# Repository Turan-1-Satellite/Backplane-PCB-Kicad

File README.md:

# Turan-1 Backplane PCB in KiCad
## About
This repository contains the KiCad 9.0 project files for the TURAN-1 Backplane PCB.

## Requirements
- KiCad 9.0 or later

## First Set up
All required custom libraries and 3D models are included as a git submodule. To clone the repository together with custom libraries, you need to recursively clone it:
```
git clone --recurse-submodules https://github.com/Turan-1-Satellite/Backplane-PCB-Kicad.git
```

## Open the Project
Open the BP-PCB-Kicad.kicad_pro file from the project root directory.

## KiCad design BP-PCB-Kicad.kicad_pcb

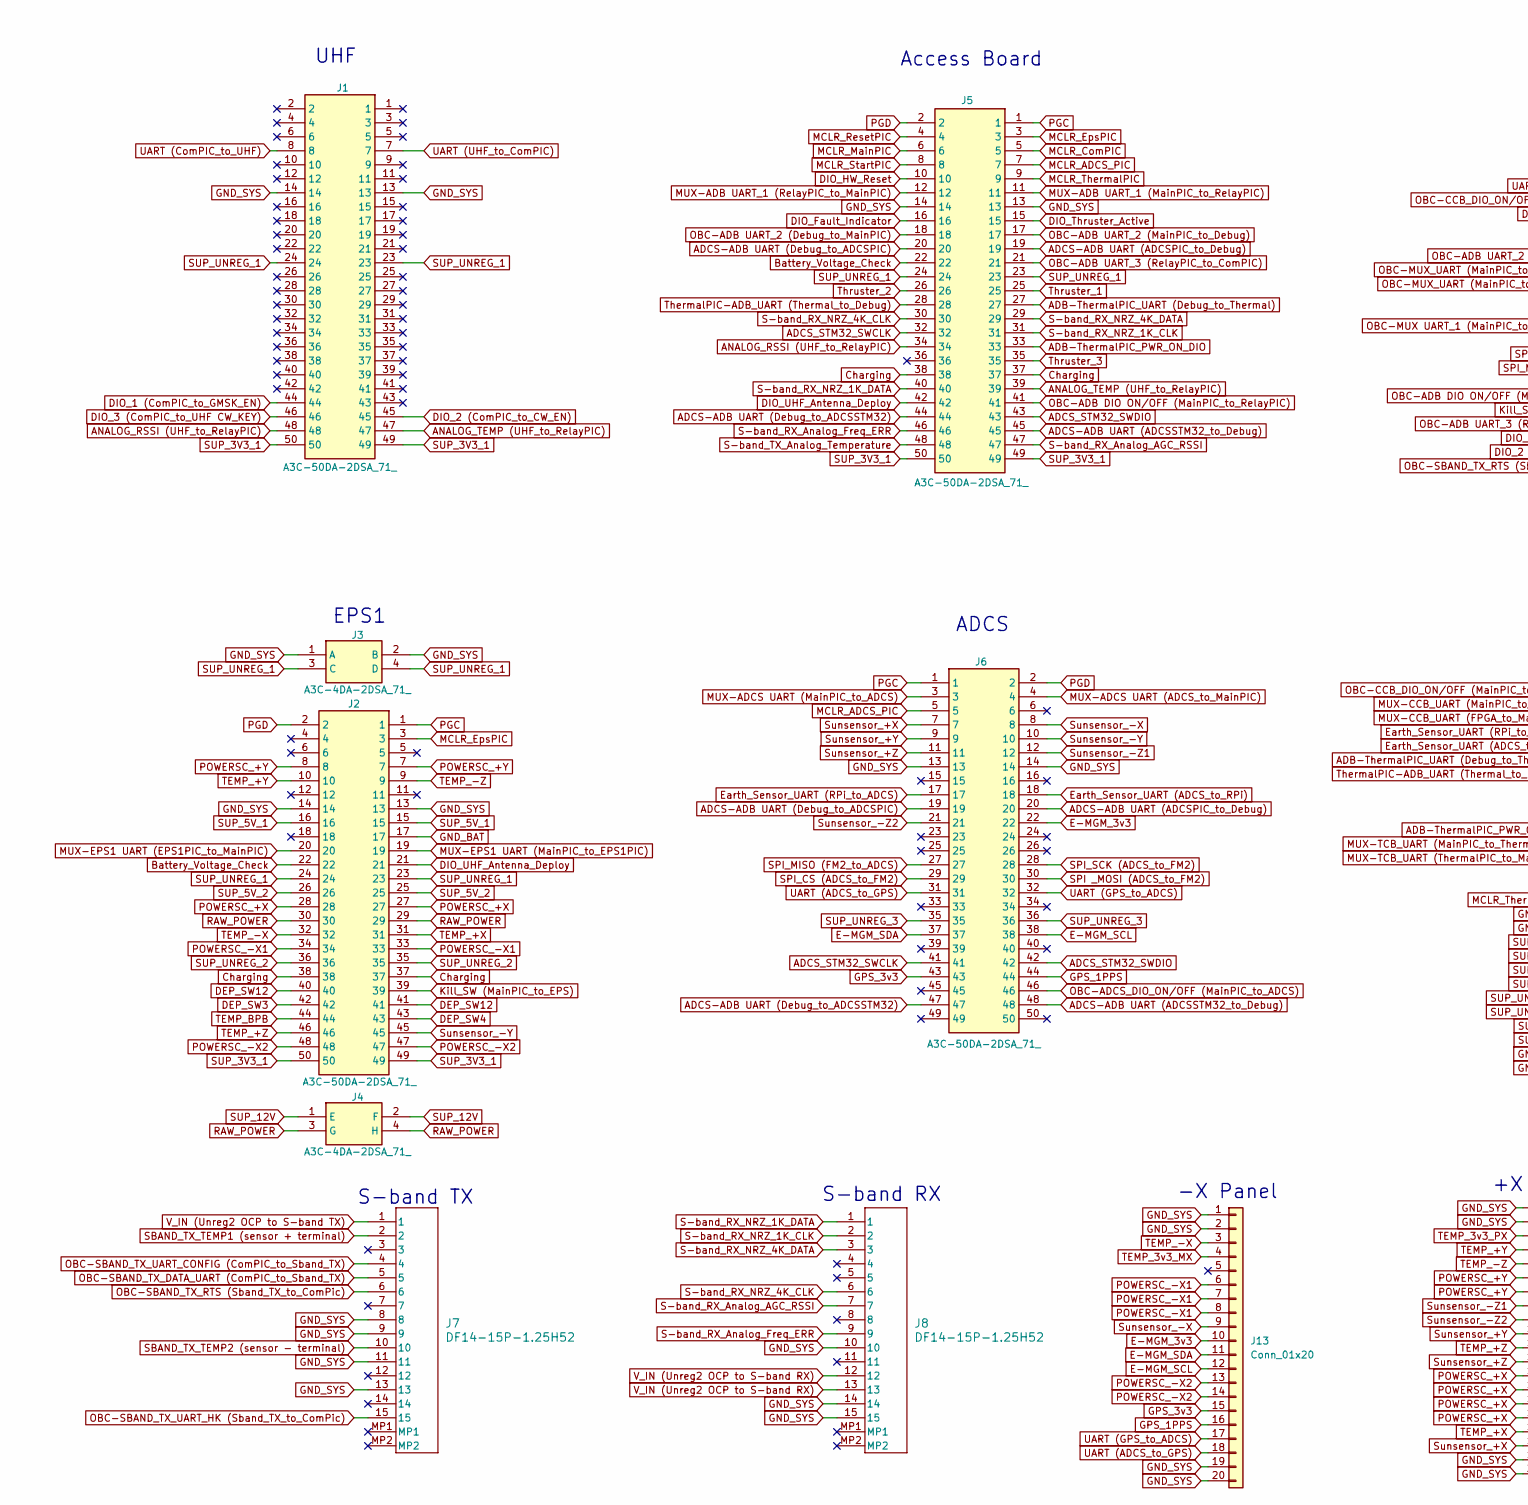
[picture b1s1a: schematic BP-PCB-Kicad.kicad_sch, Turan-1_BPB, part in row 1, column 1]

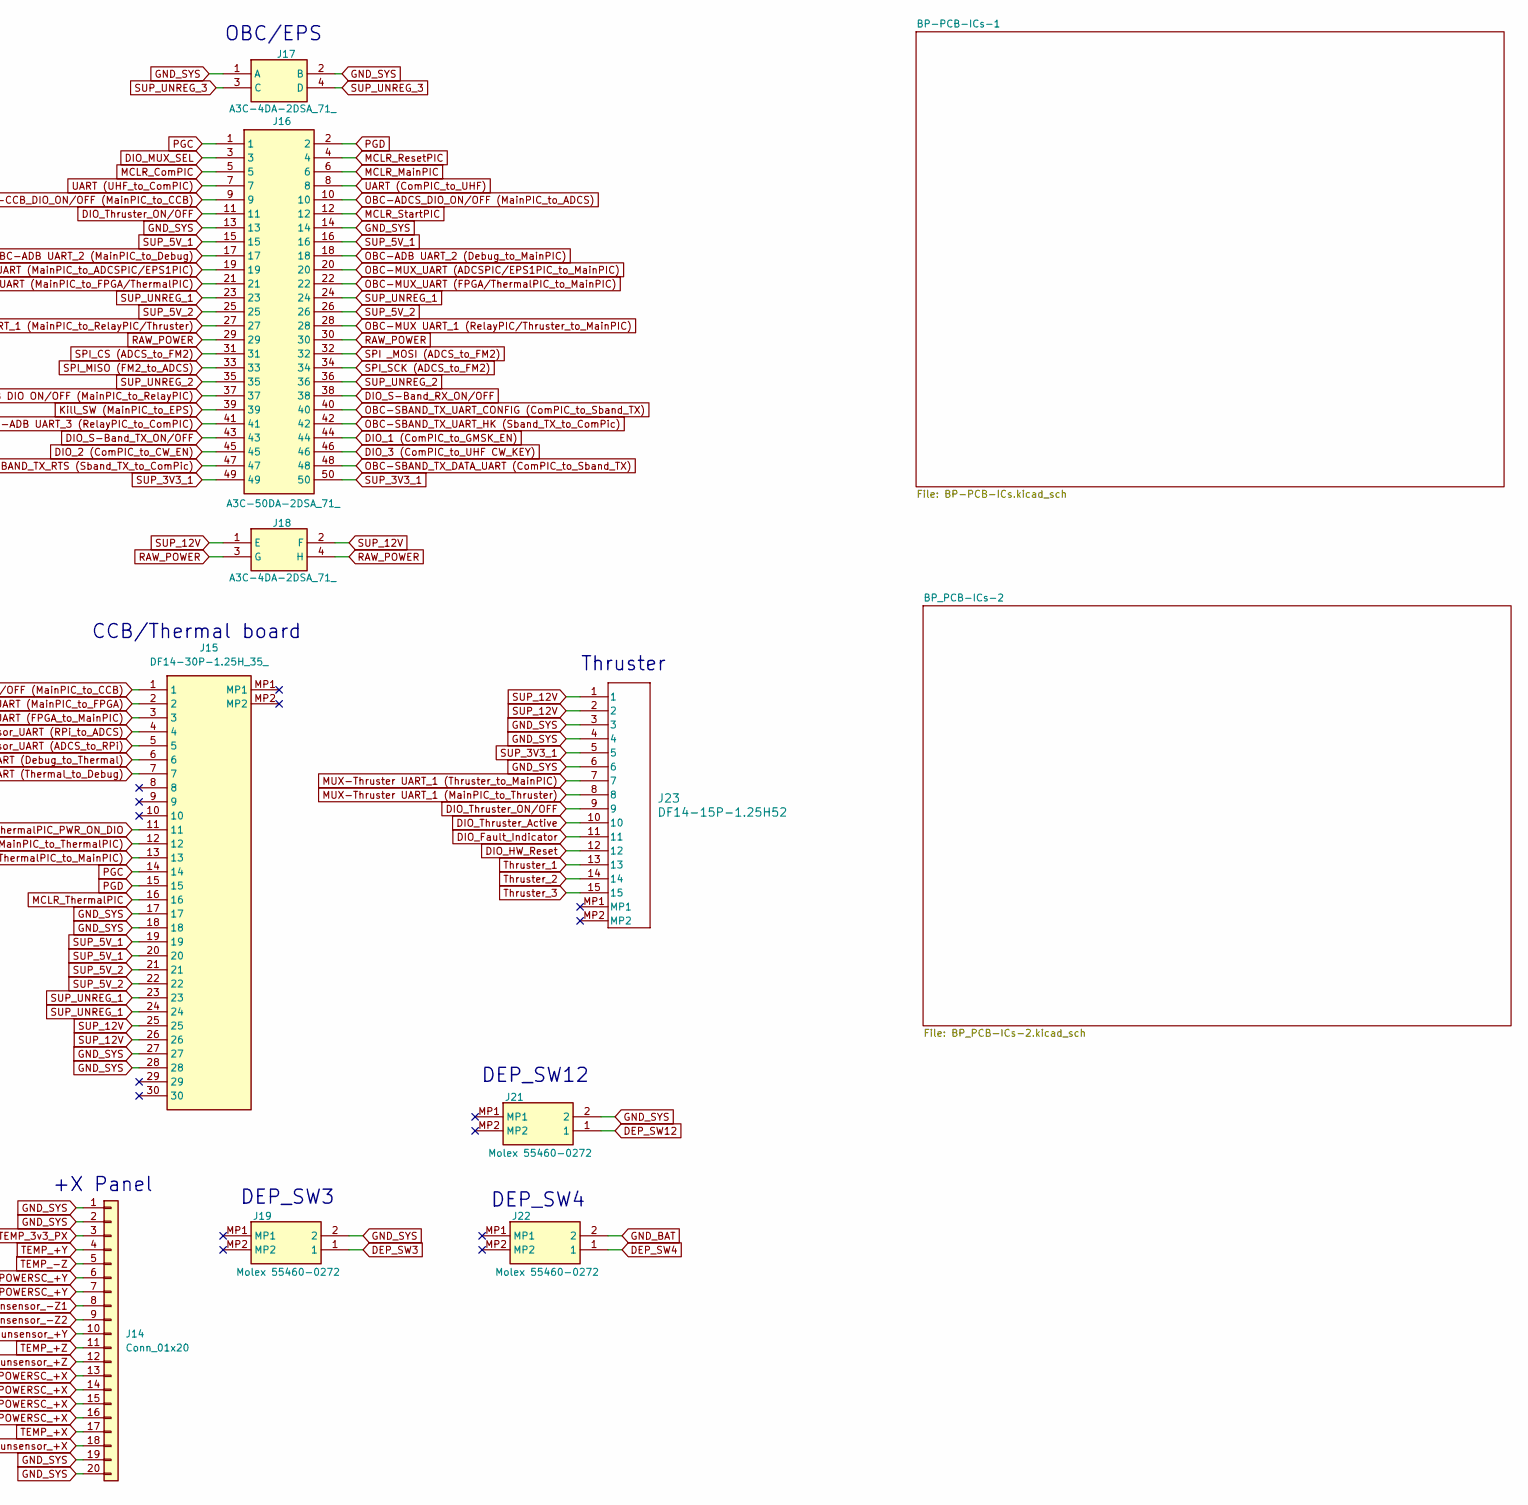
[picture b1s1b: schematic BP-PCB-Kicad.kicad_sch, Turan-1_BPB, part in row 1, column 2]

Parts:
J1, J2, J5: A3C-50DA-2DSA_71_; Hirose_A3C-50DA-2DSC(71)_Mirrored; Mouser Part Number 798-A3C-50DA-2DSA71
J3, J4: A3C-4DA-2DSA_71_; Hirose_A3C-4DA-2DSA(71)_Mirrored; Mouser Part Number 798-A3C-4DA-2DSA71
J6, J16: A3C-50DA-2DSA_71_; Hirose_A3C-50DA-2DSC(71); Mouser Part Number 798-A3C-50DA-2DSA71
J7, J8, J23: DF14-15P-1.25H52; Hirose_DF14-15P-1.25H(52)
J13: Conn_01x20; PSR-420253-10
J14: Conn_01x20; PSR-420253-10_Mirrored
J15: DF14-30P-1.25H_35_; Hirose_DF14-30P-1.25H(35); Mouser Part Number 798-DF1430P125H35
J17, J18: A3C-4DA-2DSA_71_; Hirose_A3C-4DA-2DSA(71); Mouser Part Number 798-A3C-4DA-2DSA71
J19, J21, J22: Molex 55460-0272; Molex_0554600272; Mouser Part Number 538-55460-0272

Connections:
V_IN (Unreg2 OCP to S-band RX): J8.12, J8.13; also elsewhere on the board
V_IN (Unreg2 OCP to S-band TX): J7.1; also elsewhere on the board
ADB-ThermalPIC_PWR_ON_DIO: J5.33, J15.11
ADB-ThermalPIC_UART (Debug_to_Thermal): J5.27, J15.6
ADCS-ADB UART (ADCSPIC_to_Debug): J5.19, J6.20
ADCS-ADB UART (ADCSSTM32_to_Debug): J5.45, J6.48
ADCS-ADB UART (Debug_to_ADCSPIC): J5.20, J6.19
ADCS-ADB UART (Debug_to_ADCSSTM32): J5.44, J6.47
ADCS_STM32_SWCLK: J5.32, J6.41
ADCS_STM32_SWDIO: J5.43, J6.42
ANALOG_RSSI (UHF_to_RelayPIC): J1.48, J5.34
ANALOG_TEMP (UHF_to_RelayPIC): J1.47, J5.39
Battery_Voltage_Check: J2.22, J5.22
Charging: J2.37, J2.38, J5.37, J5.38
DEP_SW3: J2.42, J19.1
DEP_SW4: J2.43, J22.1
DEP_SW12: J2.40, J2.41, J21.1
DIO_1 (ComPIC_to_GMSK_EN): J1.44, J16.44
DIO_2 (ComPIC_to_CW_EN): J1.45, J16.45
DIO_3 (ComPIC_to_UHF CW_KEY): J1.46, J16.46
DIO_Fault_Indicator: J5.16, J23.11
DIO_HW_Reset: J5.10, J23.12
DIO_MUX_SEL: J16.3; also elsewhere on the board
DIO_S-Band_RX_ON/OFF: J16.38; also elsewhere on the board
DIO_S-Band_TX_ON/OFF: J16.43; also elsewhere on the board
DIO_Thruster_Active: J5.15, J23.10
DIO_Thruster_ON/OFF: J16.11, J23.9
DIO_UHF_Antenna_Deploy: J2.21, J5.42
E-MGM_3v3: J6.22, J13.10
E-MGM_SCL: J6.38, J13.12
E-MGM_SDA: J6.37, J13.11
Earth_Sensor_UART (ADCS_to_RPi): J6.18, J15.5
Earth_Sensor_UART (RPi_to_ADCS): J6.17, J15.4
GND_BAT: J2.17, J22.2
GND_SYS: J1.13, J1.14, J2.13, J2.14, J3.1 (A), J3.2 (B), J5.13, J5.14, J6.13, J6.14, J7.8, J7.9, J7.11, J7.13, J8.10, J8.14, J8.15, J13.1, J13.2, J13.19, J13.20, J14.1, J14.2, J14.19, J14.20, J15.17, J15.18, J15.27, J15.28, J16.13, J16.14, J17.1 (A), J17.2 (B), J19.2, J21.2, J23.3, J23.4, J23.6; also elsewhere on the board
GPS_1PPS: J6.44, J13.16
GPS_3v3: J6.43, J13.15
Kill_SW (MainPIC_to_EPS): J2.39, J16.39
MCLR_ADCS_PIC: J5.7, J6.5
MCLR_ComPIC: J5.5, J16.5
MCLR_EpsPIC: J2.3, J5.3
MCLR_MainPIC: J5.6, J16.6
MCLR_ResetPIC: J5.4, J16.4
MCLR_StartPIC: J5.8, J16.12
MCLR_ThermalPIC: J5.9, J15.16
MUX-ADB UART_1 (MainPIC_to_RelayPIC): J5.11; also elsewhere on the board
MUX-ADB UART_1 (RelayPIC_to_MainPIC): J5.12; also elsewhere on the board
MUX-ADCS UART (ADCS_to_MainPIC): J6.4; also elsewhere on the board
MUX-ADCS UART (MainPIC_to_ADCS): J6.3; also elsewhere on the board
MUX-CCB_UART (FPGA_to_MainPIC): J15.3; also elsewhere on the board
MUX-CCB_UART (MainPIC_to_FPGA): J15.2; also elsewhere on the board
MUX-EPS1 UART (EPS1PIC_to_MainPIC): J2.20; also elsewhere on the board
MUX-EPS1 UART (MainPIC_to_EPS1PIC): J2.19; also elsewhere on the board
MUX-TCB_UART (MainPIC_to_ThermalPIC): J15.12; also elsewhere on the board
MUX-TCB_UART (ThermalPIC_to_MainPIC): J15.13; also elsewhere on the board
MUX-Thruster UART_1 (MainPIC_to_Thruster): J23.8; also elsewhere on the board
MUX-Thruster UART_1 (Thruster_to_MainPIC): J23.7; also elsewhere on the board
OBC-ADB DIO ON/OFF (MainPIC_to_RelayPIC): J5.41, J16.37
OBC-ADB UART_2 (Debug_to_MainPIC): J5.18, J16.18
OBC-ADB UART_2 (MainPIC_to_Debug): J5.17, J16.17
OBC-ADB UART_3 (RelayPIC_to_ComPIC): J5.21, J16.41
OBC-ADCS_DIO_ON/OFF (MainPIC_to_ADCS): J6.46, J16.10
OBC-CCB_DIO_ON/OFF (MainPIC_to_CCB): J15.1, J16.9
OBC-MUX UART_1 (MainPIC_to_RelayPIC/Thruster): J16.27; also elsewhere on the board
OBC-MUX UART_1 (RelayPIC/Thruster_to_MainPIC): J16.28; also elsewhere on the board
OBC-MUX_UART (ADCSPIC/EPS1PIC_to_MainPIC): J16.20; also elsewhere on the board
OBC-MUX_UART (FPGA/ThermalPIC_to_MainPIC): J16.22; also elsewhere on the board
OBC-MUX_UART (MainPIC_to_ADCSPIC/EPS1PIC): J16.19; also elsewhere on the board
OBC-MUX_UART (MainPIC_to_FPGA/ThermalPIC): J16.21; also elsewhere on the board
OBC-SBAND_TX_DATA_UART (ComPIC_to_Sband_TX): J7.5, J16.48
OBC-SBAND_TX_RTS (Sband_TX_to_ComPic): J7.6, J16.47
OBC-SBAND_TX_UART_CONFIG (ComPIC_to_Sband_TX): J7.4, J16.40
OBC-SBAND_TX_UART_HK (Sband_TX_to_ComPic): J7.15, J16.42
PGC: J2.1, J5.1, J6.1, J15.14, J16.1
PGD: J2.2, J5.2, J6.2, J15.15, J16.2
POWERSC_+X: J2.27, J2.28, J14.13, J14.14, J14.15, J14.16
POWERSC_+Y: J2.7, J2.8, J14.6, J14.7
POWERSC_-X1: J2.33, J2.34, J13.6, J13.7, J13.8
POWERSC_-X2: J2.47, J2.48, J13.13, J13.14
RAW_POWER: J2.29, J2.30, J4.3 (G), J4.4 (H), J16.29, J16.30, J18.3 (G), J18.4 (H)
S-band_RX_Analog_AGC_RSSI: J5.47, J8.7
S-band_RX_Analog_Freq_ERR: J5.46, J8.9
S-band_RX_NRZ_1K_CLK: J5.31, J8.2
S-band_RX_NRZ_1K_DATA: J5.40, J8.1
S-band_RX_NRZ_4K_CLK: J5.30, J8.6
S-band_RX_NRZ_4K_DATA: J5.29, J8.3
S-band_TX_Analog_Temperature: J5.48, J7.10; also elsewhere on the board
SBAND_TX_TEMP1 (sensor + terminal): J7.2; also elsewhere on the board
SPI _MOSI (ADCS_to_FM2): J6.30, J16.32
SPI_CS (ADCS_to_FM2): J6.29, J16.31
SPI_MISO (FM2_to_ADCS): J6.27, J16.33
SPI_SCK (ADCS_to_FM2): J6.28, J16.34
SUP_3V3_1: J1.49, J1.50, J2.49, J2.50, J5.49, J5.50, J16.49, J16.50, J23.5; also elsewhere on the board
SUP_5V_1: J2.15, J2.16, J15.19, J15.20, J16.15, J16.16; also elsewhere on the board
SUP_5V_2: J2.25, J2.26, J15.21, J15.22, J16.25, J16.26
SUP_12V: J4.1 (E), J4.2 (F), J15.25, J15.26, J18.1 (E), J18.2 (F), J23.1, J23.2
SUP_UNREG_1: J1.23, J1.24, J2.23, J2.24, J3.3 (C), J3.4 (D), J5.23, J5.24, J15.23, J15.24, J16.23, J16.24
SUP_UNREG_2: J2.35, J2.36, J16.35, J16.36; also elsewhere on the board
SUP_UNREG_3: J6.35, J6.36, J17.3 (C), J17.4 (D)
Sunsensor_+X: J6.7, J14.18
Sunsensor_+Y: J6.9, J14.10
Sunsensor_+Z: J6.11, J14.12
Sunsensor_-X: J6.8, J13.9
Sunsensor_-Y: J2.45, J6.10
Sunsensor_-Z1: J6.12, J14.8
Sunsensor_-Z2: J6.21, J14.9
TEMP_3v3_MX: J13.4; also elsewhere on the board
TEMP_3v3_PX: J14.3; also elsewhere on the board
TEMP_+X: J2.31, J14.17
TEMP_+Y: J2.10, J14.4
TEMP_+Z: J2.46, J14.11
TEMP_-X: J2.32, J13.3
TEMP_-Z: J2.9, J14.5
TEMP_BPB: J2.44; also elsewhere on the board
ThermalPIC-ADB_UART (Thermal_to_Debug): J5.28, J15.7
Thruster_1: J5.25, J23.13
Thruster_2: J5.26, J23.14
Thruster_3: J5.35, J23.15
UART (ADCS_to_GPS): J6.31, J13.18
UART (ComPIC_to_UHF): J1.8, J16.8
UART (GPS_to_ADCS): J6.32, J13.17
UART (UHF_to_ComPIC): J1.7, J16.7

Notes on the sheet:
DEP_SW4
OBC/EPS
ADCS
S-band TX
EPS1
DEP_SW3
+X Panel
CCB/Thermal board
DEP_SW12
S-band RX
UHF
Access Board
Thruster
-X Panel

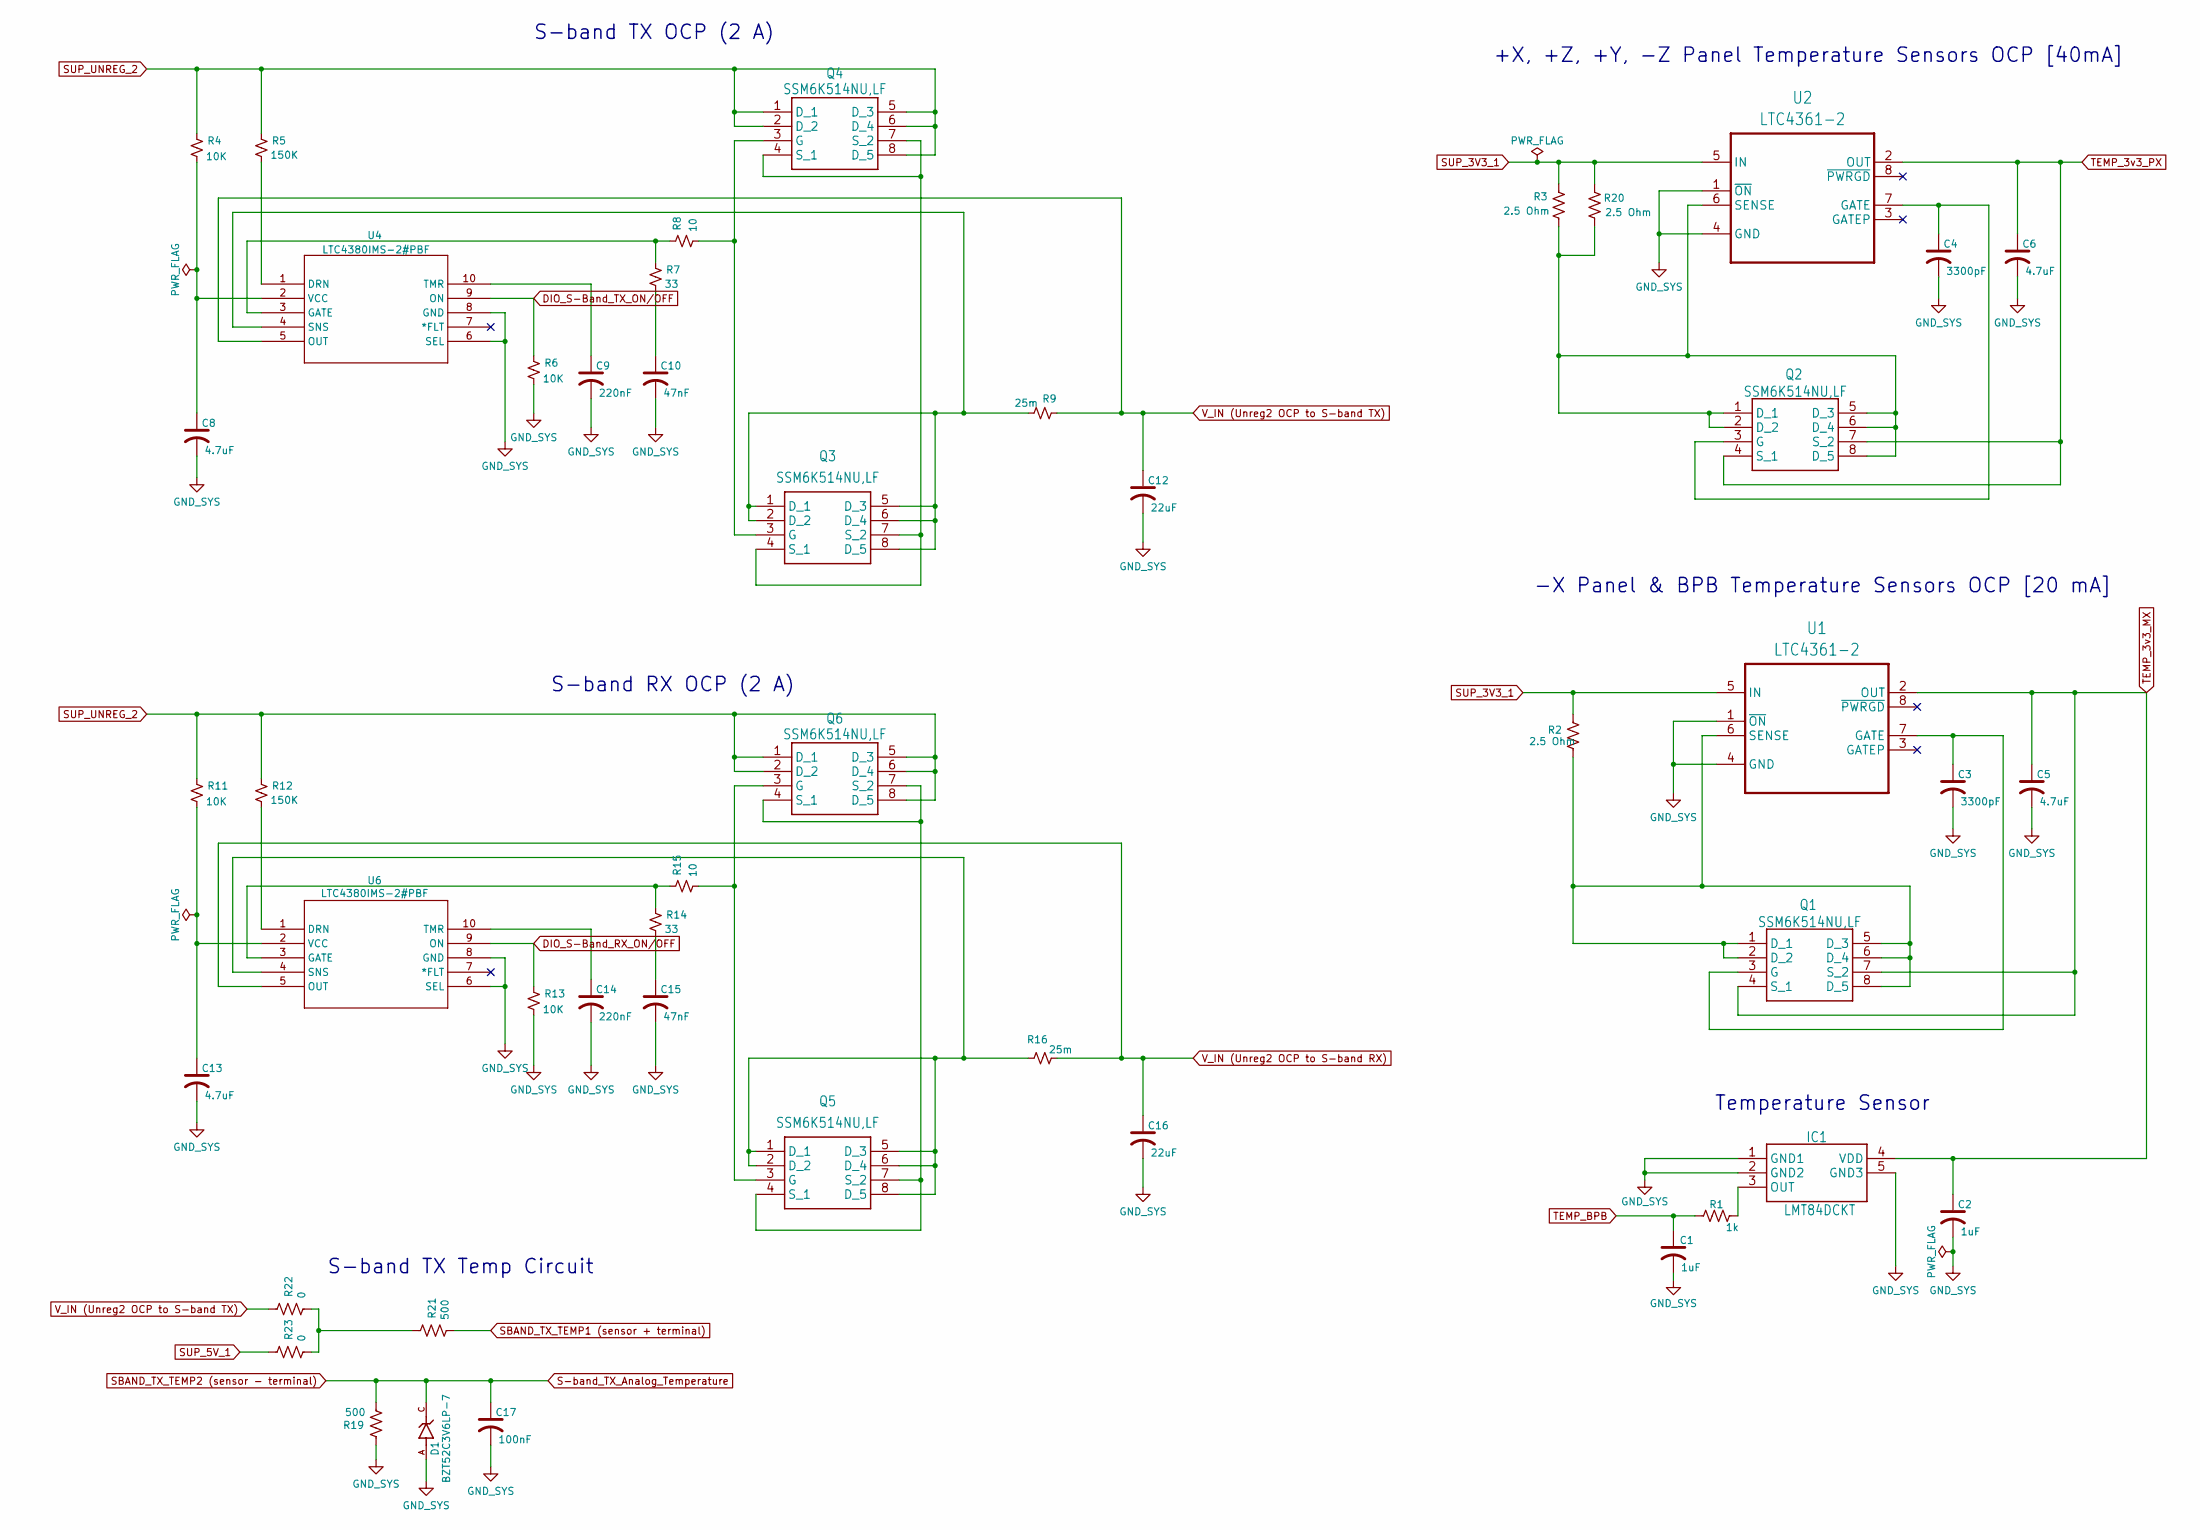
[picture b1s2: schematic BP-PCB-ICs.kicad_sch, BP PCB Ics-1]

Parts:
C1, C2: 1uF; C_0805_2012Metric; LCSC Part C1712
C3, C4: 3300pF; C_0805_2012Metric; LCSC Part C77062
C5, C6, C8, C13: 4.7uF; C_0805_2012Metric; LCSC Part C1746
C9, C14: 220nF; C_0805_2012Metric; LCSC Part C1770
C10, C15: 47nF; C_0805_2012Metric; LCSC Part C1745
C12, C16: 22uF; C_0805_2012Metric; LCSC Part C45783
C17: 100nF; C_0805_2012Metric; LCSC Part C29926
D1: BZT52C3V6LP-7; DIO_BZT52C3V6LP-7; LCSC Part C151430
IC1: LMT84DCKT; LCSC Part C2860524
Q1, Q2, Q3, Q4, Q5, Q6: SSM6K514NU,LF; SSM6K514NULF; LCSC Part C6235373
R1: 1k; R_0805_2012Metric; LCSC Part C702831
R2, R3, R20: 2.5 Ohm; R_0805_2012Metric; LCSC Part C409739
R4, R6, R11, R13: 10K; R_0805_2012Metric; LCSC Part C702829
R5, R12: 150K; R_0805_2012Metric; LCSC Part C17470
R7, R14: 33; R_0805_2012Metric; LCSC Part C49330262
R8, R15: 10; R_0805_2012Metric; LCSC Part C702857
R9, R16: 25m; R_0805_2012Metric; LCSC Part C858607
R19, R21: 500; R_0805_2012Metric; LCSC Part C2828711
R22: 0; R_0805_2012Metric
R23: 0; R_0805_2012Metric; LCSC Part C702869
U1, U2: LTC4361-2; LTC4361HTS8; LCSC Part C688273
U4, U6: LTC4380IMS-2#PBF; LCSC Part C688471

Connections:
V_IN (Unreg2 OCP to S-band RX): C16.1, R16.2, U6.5 (OUT); also elsewhere on the board
V_IN (Unreg2 OCP to S-band TX): C12.1, R9.2, R22.1, U4.5 (OUT); also elsewhere on the board
DIO_S-Band_RX_ON/OFF: R13.1, U6.9 (ON); also elsewhere on the board
DIO_S-Band_TX_ON/OFF: R6.1, U4.9 (ON); also elsewhere on the board
GND_SYS: C1.2, C2.2, C3.2, C4.2, C5.2, C6.2, C8.2, C9.2, C10.2, C12.2, C13.2, C14.2, C15.2, C16.2, C17.2, D1.A, IC1.1 (GND1), IC1.2 (GND2), IC1.5 (GND3), R6.2, R13.2, R19.1, U1.1 (~ON), U1.4 (GND), U2.1 (~ON), U2.4 (GND), U4.6 (SEL), U4.8 (GND), U6.6 (SEL), U6.8 (GND); also elsewhere on the board
unnamed: C10.1, R7.2
unnamed: C15.1, R14.2
unnamed: IC1.3 (OUT), R1.2
unnamed: Q1.1 (D_1), Q1.2 (D_2), Q1.5 (D_3), Q1.6 (D_4), Q1.8 (D_5), R2.2, U1.6 (SENSE)
unnamed: C3.1, Q1.3 (G), U1.7 (GATE)
unnamed: Q2.1 (D_1), Q2.2 (D_2), Q2.5 (D_3), Q2.6 (D_4), Q2.8 (D_5), R3.2, R20.2, U2.6 (SENSE)
unnamed: C4.1, Q2.3 (G), U2.7 (GATE)
unnamed: Q3.1 (D_1), Q3.2 (D_2), Q3.5 (D_3), Q3.6 (D_4), Q3.8 (D_5), R9.1, U4.4 (SNS)
unnamed: Q3.3 (G), Q4.3 (G), R8.2
unnamed: Q3.4 (S_1), Q3.7 (S_2), Q4.4 (S_1), Q4.7 (S_2)
unnamed: Q5.1 (D_1), Q5.2 (D_2), Q5.5 (D_3), Q5.6 (D_4), Q5.8 (D_5), R16.1, U6.4 (SNS)
unnamed: Q5.3 (G), Q6.3 (G), R15.2
unnamed: Q5.4 (S_1), Q5.7 (S_2), Q6.4 (S_1), Q6.7 (S_2)
unnamed: R21.1, R22.2, R23.2
unnamed: R5.2, U4.1 (DRN)
unnamed: R7.1, R8.1, U4.3 (GATE)
unnamed: C9.1, U4.10 (TMR)
unnamed: C8.1, R4.2, U4.2 (VCC)
unnamed: R12.2, U6.1 (DRN)
unnamed: R14.1, R15.1, U6.3 (GATE)
unnamed: C14.1, U6.10 (TMR)
unnamed: C13.1, R11.2, U6.2 (VCC)
S-band_TX_Analog_Temperature: C17.1, D1.C, R19.2; also elsewhere on the board
SBAND_TX_TEMP1 (sensor + terminal): R21.2; also elsewhere on the board
SUP_3V3_1: R2.1, R3.1, R20.1, U1.5 (IN), U2.5 (IN); also elsewhere on the board
SUP_5V_1: R23.1; also elsewhere on the board
SUP_UNREG_2: Q4.1 (D_1), Q4.2 (D_2), Q4.5 (D_3), Q4.6 (D_4), Q4.8 (D_5), Q6.1 (D_1), Q6.2 (D_2), Q6.5 (D_3), Q6.6 (D_4), Q6.8 (D_5), R4.1, R5.1, R11.1, R12.1; also elsewhere on the board
TEMP_3v3_MX: C2.1, C5.1, IC1.4 (VDD), Q1.4 (S_1), Q1.7 (S_2), U1.2 (OUT); also elsewhere on the board
TEMP_3v3_PX: C6.1, Q2.4 (S_1), Q2.7 (S_2), U2.2 (OUT); also elsewhere on the board
TEMP_BPB: C1.1, R1.1; also elsewhere on the board

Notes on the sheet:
S-band TX Temp Circuit
Temperature Sensor
+X, +Z, +Y, -Z Panel Temperature Sensors OCP [40mA]
-X Panel & BPB Temperature Sensors OCP [20 mA]
S-band TX OCP (2 A)
S-band RX OCP (2 A)

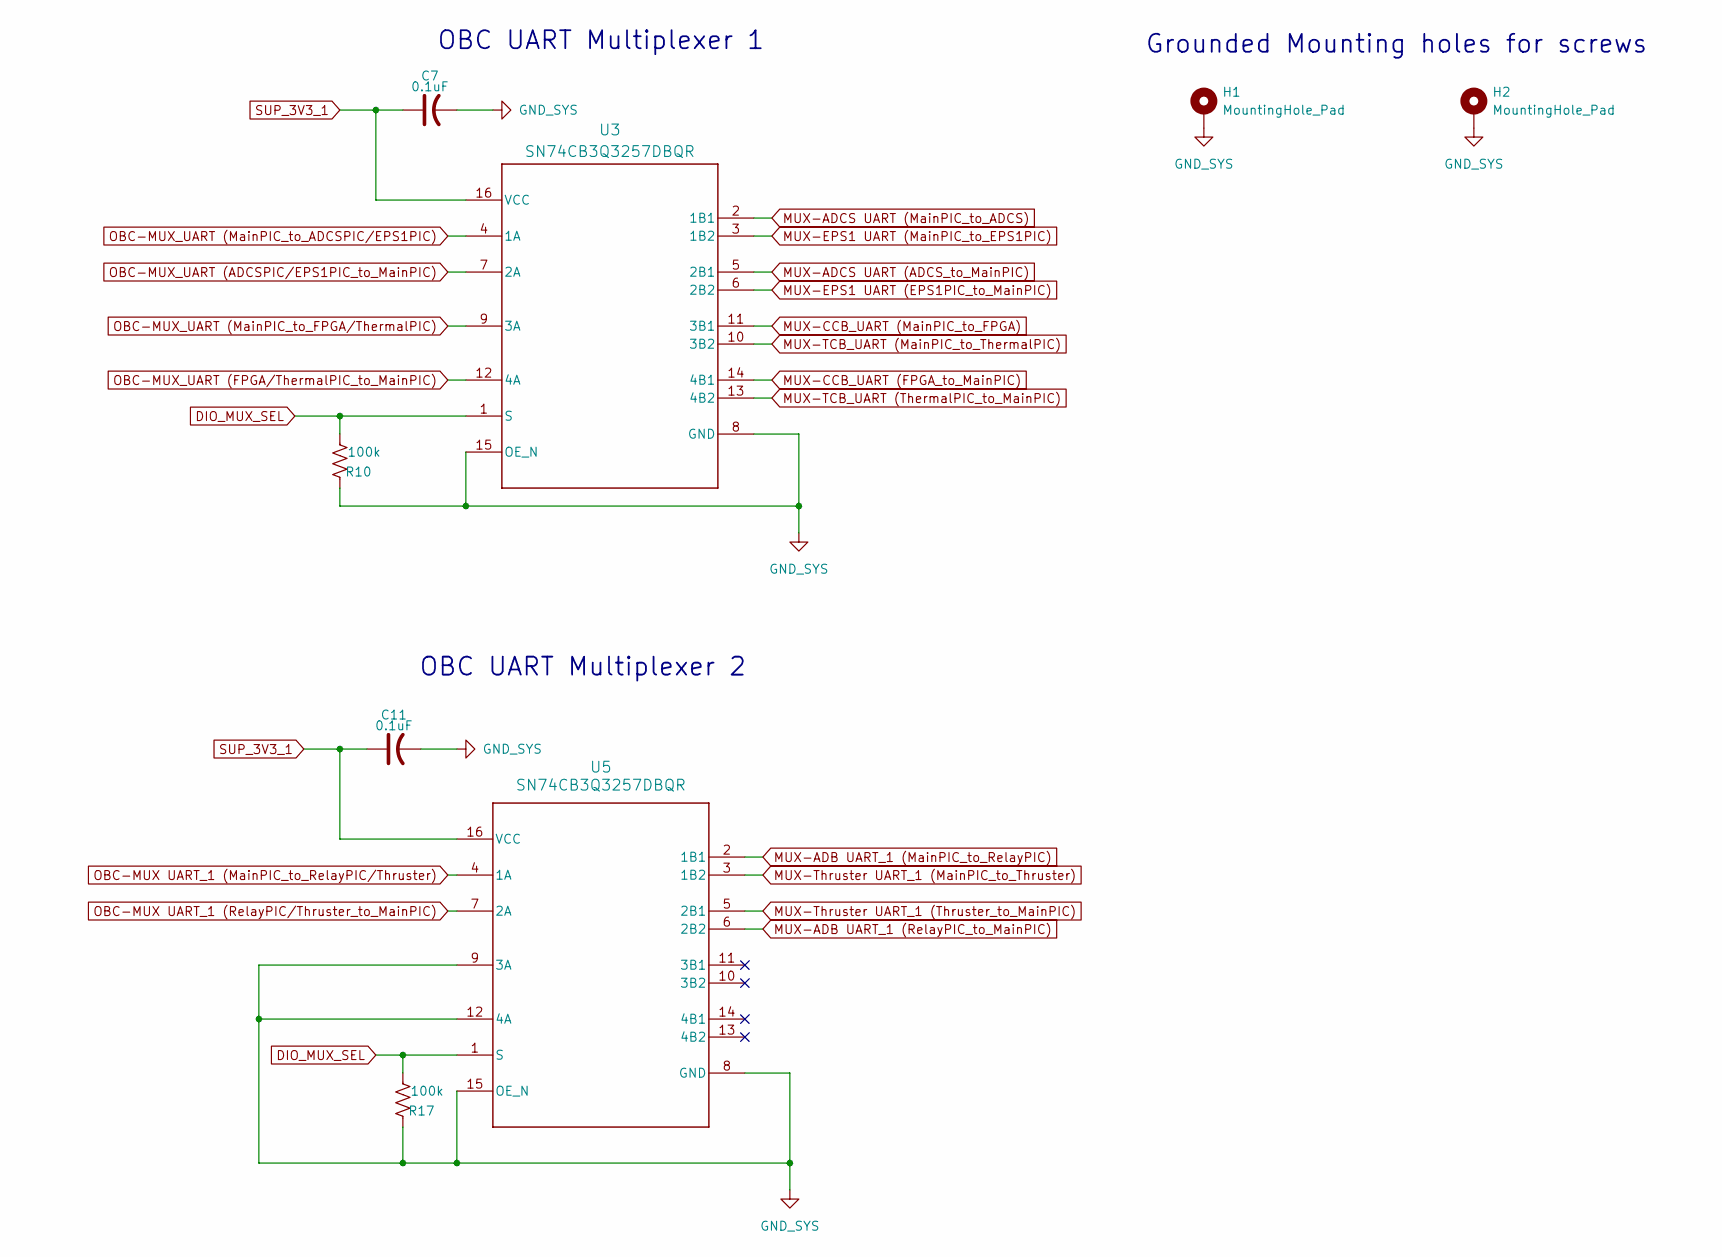
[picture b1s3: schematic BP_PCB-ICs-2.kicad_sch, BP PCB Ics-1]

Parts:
C7, C11: 0.1uF; C_0805_2012Metric; LCSC Part C1711
H1, H2: MountingHole_Pad; MountingHole_2.7mm_Pad
R10, R17: 100k; R_0805_2012Metric; LCSC Part C409739
U3, U5: SN74CB3Q3257DBQR; LCSC Part C7138

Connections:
DIO_MUX_SEL: R10.2, R17.2, U3.1 (S), U5.1 (S); also elsewhere on the board
GND_SYS: C7.2, C11.2, H1.1, H2.1, R10.1, R17.1, U3.8 (GND), U3.15 (OE_N), U5.8 (GND), U5.9 (3A), U5.12 (4A), U5.15 (OE_N); also elsewhere on the board
MUX-ADB UART_1 (MainPIC_to_RelayPIC): U5.2 (1B1); also elsewhere on the board
MUX-ADB UART_1 (RelayPIC_to_MainPIC): U5.6 (2B2); also elsewhere on the board
MUX-ADCS UART (ADCS_to_MainPIC): U3.5 (2B1); also elsewhere on the board
MUX-ADCS UART (MainPIC_to_ADCS): U3.2 (1B1); also elsewhere on the board
MUX-CCB_UART (FPGA_to_MainPIC): U3.14 (4B1); also elsewhere on the board
MUX-CCB_UART (MainPIC_to_FPGA): U3.11 (3B1); also elsewhere on the board
MUX-EPS1 UART (EPS1PIC_to_MainPIC): U3.6 (2B2); also elsewhere on the board
MUX-EPS1 UART (MainPIC_to_EPS1PIC): U3.3 (1B2); also elsewhere on the board
MUX-TCB_UART (MainPIC_to_ThermalPIC): U3.10 (3B2); also elsewhere on the board
MUX-TCB_UART (ThermalPIC_to_MainPIC): U3.13 (4B2); also elsewhere on the board
MUX-Thruster UART_1 (MainPIC_to_Thruster): U5.3 (1B2); also elsewhere on the board
MUX-Thruster UART_1 (Thruster_to_MainPIC): U5.5 (2B1); also elsewhere on the board
OBC-MUX UART_1 (MainPIC_to_RelayPIC/Thruster): U5.4 (1A); also elsewhere on the board
OBC-MUX UART_1 (RelayPIC/Thruster_to_MainPIC): U5.7 (2A); also elsewhere on the board
OBC-MUX_UART (ADCSPIC/EPS1PIC_to_MainPIC): U3.7 (2A); also elsewhere on the board
OBC-MUX_UART (FPGA/ThermalPIC_to_MainPIC): U3.12 (4A); also elsewhere on the board
OBC-MUX_UART (MainPIC_to_ADCSPIC/EPS1PIC): U3.4 (1A); also elsewhere on the board
OBC-MUX_UART (MainPIC_to_FPGA/ThermalPIC): U3.9 (3A); also elsewhere on the board
SUP_3V3_1: C7.1, C11.1, U3.16 (VCC), U5.16 (VCC); also elsewhere on the board

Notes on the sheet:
Grounded Mounting holes for screws
OBC UART Multiplexer 1
OBC UART Multiplexer 2

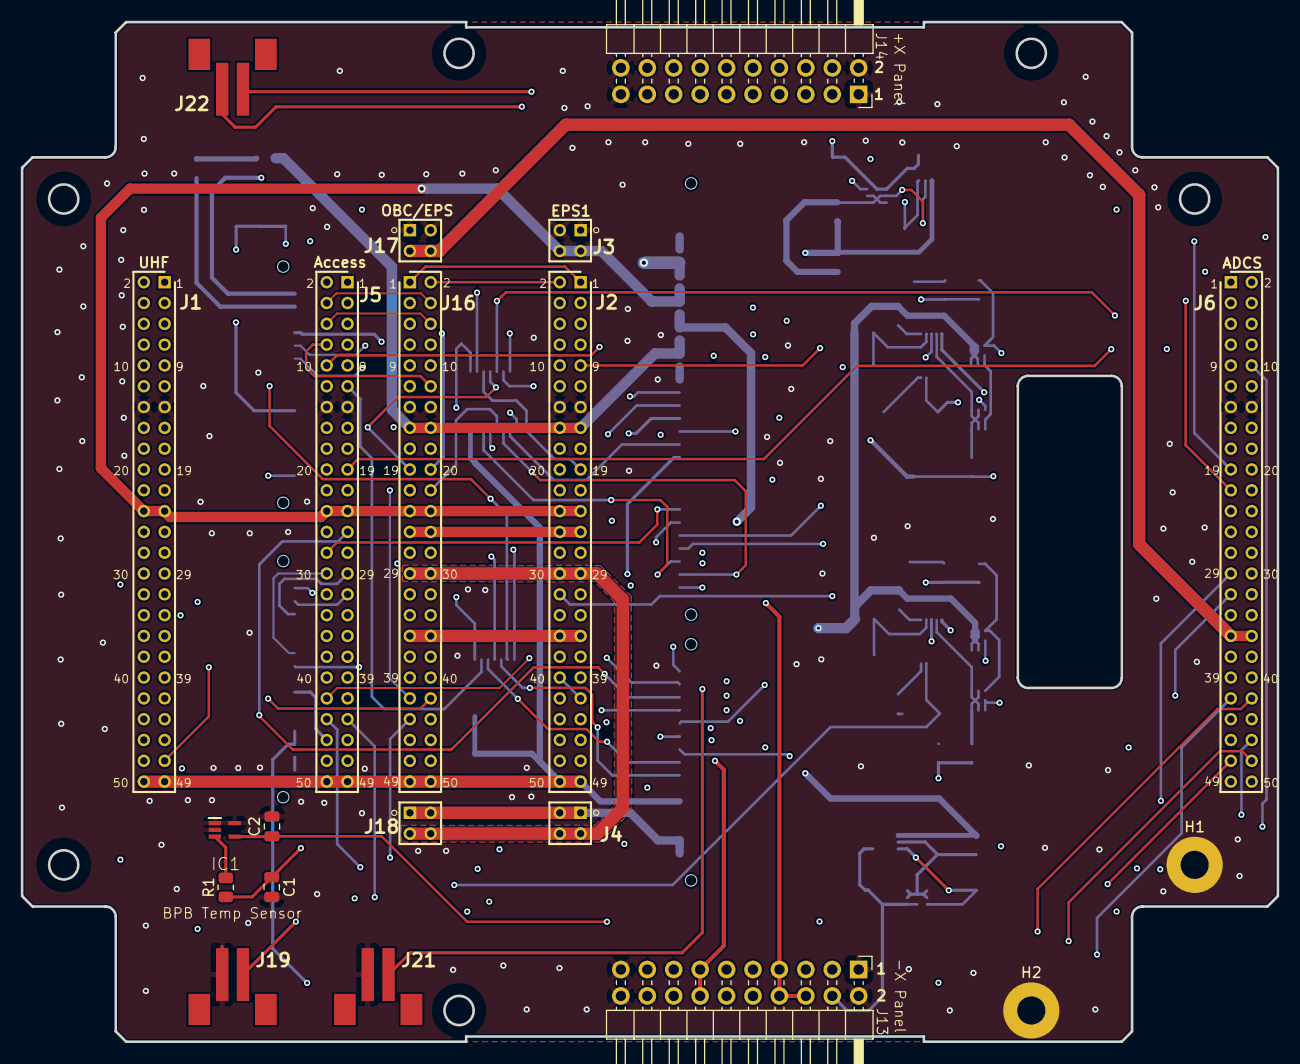
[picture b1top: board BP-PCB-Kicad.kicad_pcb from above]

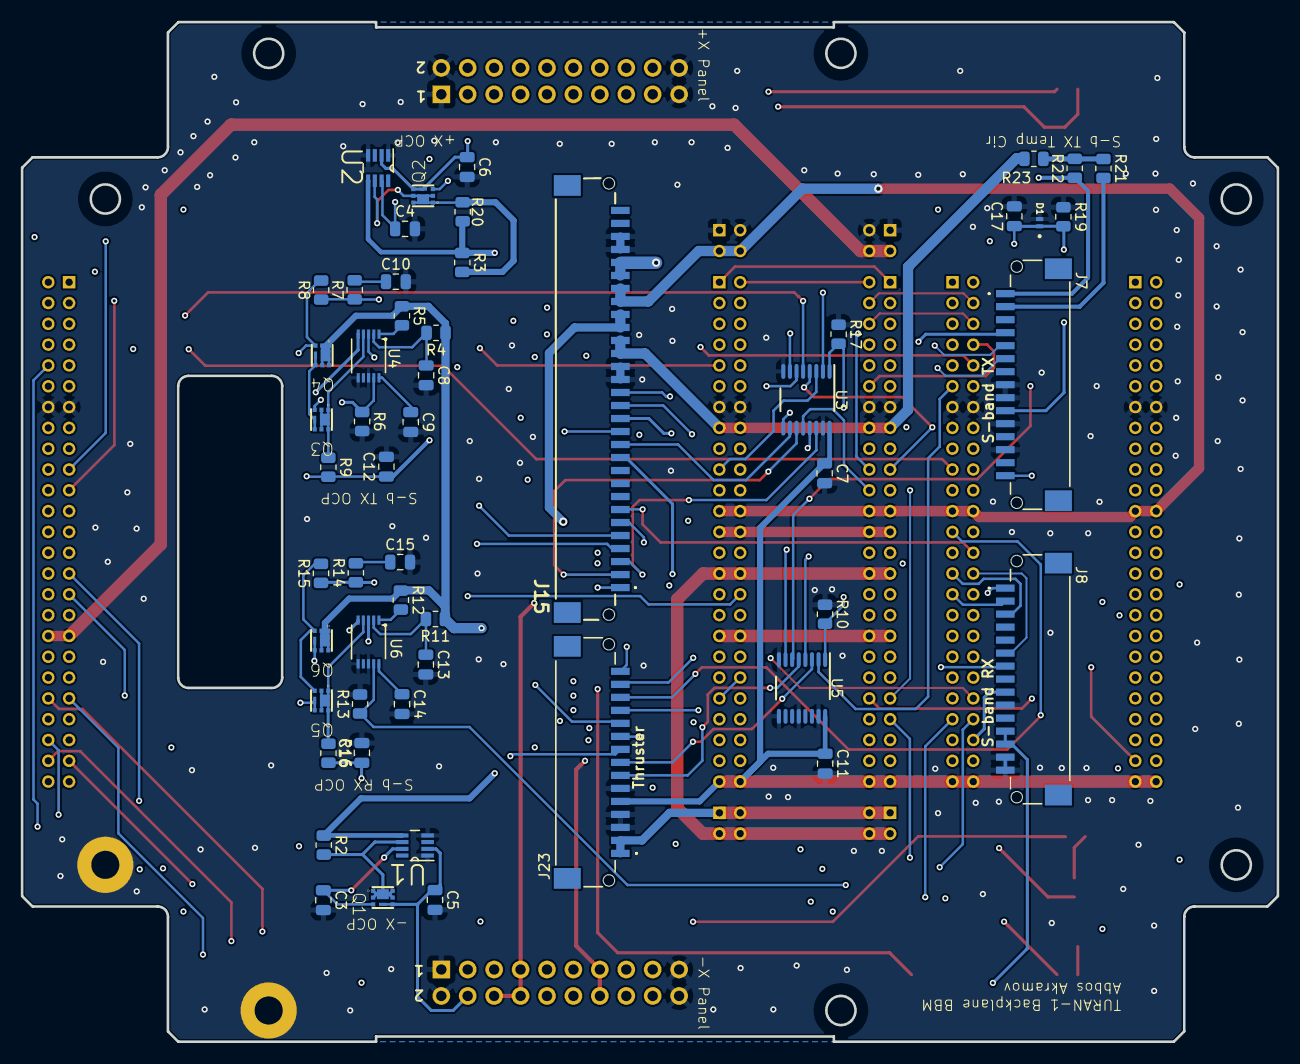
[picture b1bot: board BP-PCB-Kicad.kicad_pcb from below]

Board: 4 copper layers, 120.7 x 98.0 mm, 73 parts (53 on the bottom side), 144 nets.

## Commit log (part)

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2026-03-01 Apply backplane v2 changes from local branch
2026-03-01 All connectors mounted on BPB v2-2026-02-27 as structure's documentation
2026-03-01 ReadMe Init
2026-03-04 Git Submodule added inside <KiCad-Libaries> folder to share libraries across different projects
2026-03-04 Feature: added git submodule for kicad shared libraries
2026-03-05 Update .gitignore and symbol library table for KiCad submodule integration
2026-03-10 Customized to the latest version of the Custom KiCad-Library
2026-03-10 Revise README for Turan-1 Backplane PCB
    Updated project title and improved formatting in README.
2026-03-10 Remove CLAUDE.md from .gitignore
2026-03-11 Adjusted to libraries
2026-03-11 Customized for the latest version of lib
2026-03-23 Added ICs to schematic
2026-03-24 Fixed errors in schematics
2026-03-26 Synchronized with pin mapping table and added circuits
2026-03-26 -X temp OCP is being shared with BP
2026-03-30 PCB layout is syncronized with schematic
2026-04-04 Microelectronic components placed onto the back of BPB
2026-04-06 Routing traces of panels
2026-04-07 Finished routing v1
2026-04-09 Finished routing and NO DRC errors
2026-04-09 removed cached file
2026-04-09 removed gitignoring files
2026-04-09 Final routing v2
2026-04-10 ERC errors eleminated from schematic
2026-04-10 Update README with cloning instructions for submodules
    Added instructions for recursively cloning the repository with submodules.
2026-04-10 Fix typo in Git clone command URL
2026-04-11 Corrected OCP values in schematic and fixed PCB layout
2026-04-12 Added grounded mounting holes to schematics
2026-04-13 Polished some power lines
2026-04-13 Updated solder mask expension
2026-04-13 BBM version requested for fabrication
